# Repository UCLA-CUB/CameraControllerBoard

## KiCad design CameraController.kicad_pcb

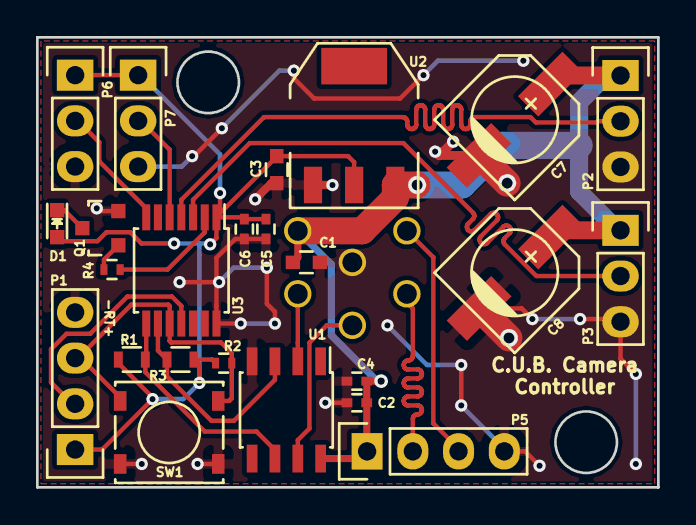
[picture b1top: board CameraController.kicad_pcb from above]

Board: 2 copper layers, 34.5 x 25.0 mm, 25 parts (1 on the bottom side), 18 nets.

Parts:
C1, C3: 4.7uF; C_0603
C2, C5: 0.001uF; C_0402
C4, C6: 0.1uF; C_0402
C7, C8: 100uF; c_elec_3.5x5.6
D1: GREEN LED; LED_0603
P1, P5: CONN_01X04; Pin_Header_Straight_1x04
P2, P3, P6, P7: CONN_01X03; Pin_Header_Straight_1x03
P4: CONN_01X06; DIN_TH_6POL
Q1: Q_NPN_BEC; SOT-23
R1, R3: 2.2K; R_0603
R2: 47K; R_0402
R4: 27K; R_0402
SW1: SW_PUSH; SW_SPST_TL3315
U1: P82B715; SOIC-8_3.9x4.9mm_Pitch1.27mm
U2: AP2114H; SOT-223
U3: MSP430G2231IN14; TSSOP-14_4.4x5mm_Pitch0.65mm

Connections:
+3V3: C3.1, C5.1, C6.1, D1.2, P1.1, P6.1, P7.1, R1.2, R2.1, R3.2, U2.2, U3.1
+5V: C1.1, C2.1, C4.1, C7.1, C8.1, P2.1, P3.1, P4.1, P5.1, U1.8, U2.3
CAM_D+: P4.4, P5.2
CAM_D-: P4.5, P5.3
GND: C1.2, C2.2, C3.2, C4.2, C5.2, C6.2, C7.2, C8.2, P1.4, P2.3, P3.3, P4.6, P5.4, P6.3, P7.3, Q1.2, SW1.1, U1.4, U2.1, U3.14
Lx_LDA: P4.2, U1.2
Ly_LCL: P4.3, U1.7
MSP_HB_LED: R4.1, U3.2
MSP_RST: P1.3, R2.2, SW1.2, U3.10
MSP_SCL: R1.1, U1.6, U3.8
MSP_SDA: R3.1, U1.3, U3.9
MSP_TEST: P1.2, U3.11
unnamed: D1.1, Q1.3
unnamed: Q1.1, R4.2
PITCH_SERVO_POT: P6.2, U3.7
PITCH_SERVO_SIG: P2.2, U3.4
YAW_SERVO_POT: P7.2, U3.5
YAW_SERVO_SIG: P3.2, U3.3

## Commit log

2018-02-01 Added BOM generation script
